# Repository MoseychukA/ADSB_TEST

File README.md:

# ADSB_TEST
ADSB decoder RP2040

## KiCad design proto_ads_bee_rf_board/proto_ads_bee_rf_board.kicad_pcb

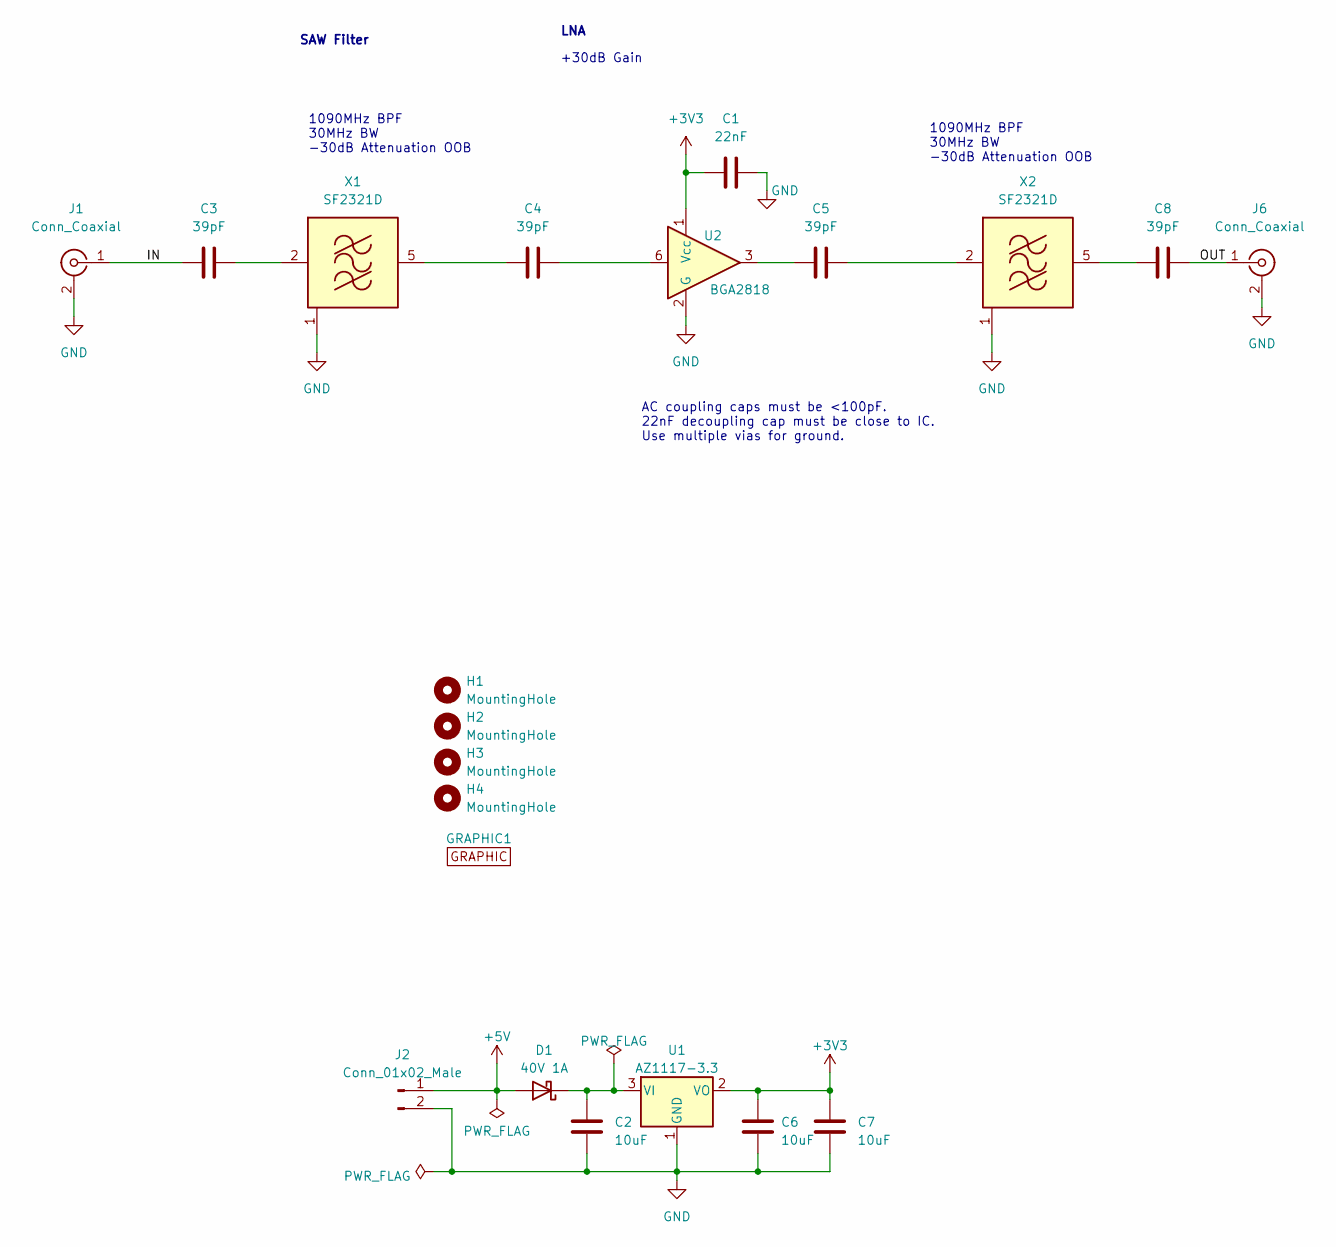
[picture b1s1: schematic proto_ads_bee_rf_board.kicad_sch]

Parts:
C1: 22nF; C_0603_1608Metric
C2, C6, C7: 10uF; C_0805_2012Metric
C3, C4, C5, C8: 39pF; C_0603_1608Metric
D1: 40V 1A; D_DO-41_SOD81_P7.62mm_Horizontal; MPN 1N5819
GRAPHIC1: Graphic; bird_with_pants_small_flipped
H1, H2, H3, H4: MountingHole; MountingHole_3.2mm_M3
J1, J6: Conn_Coaxial; SMA_Amphenol_132289_EdgeMount; MPN 132289
J2: Conn_01x02_Male; PinHeader_1x02_P2.54mm_Horizontal
U1: AZ1117-3.3; SOT-223-3_TabPin2
U2: BGA2818; SOT-363_SC-70-6
X1, X2: SF2321D; Filter_SAW-6_3.8x3.8mm; MPN SF2321D

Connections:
+3V3: C1.1, C6.1, C7.1, U1.2 (VO), U2.1 (Vcc)
+5V: D1.2 (A), J2.1
/IN: C3.1, J1.1 (In)
/OUT: C8.2, J6.1 (In)
GND: C1.2, C2.2, C6.2, C7.2, J1.2 (Ext), J2.2, J6.2 (Ext), U1.1 (GND), U2.2 (G), U2.4 (G), U2.5 (G), X1.1 (GND), X1.3 (GND), X1.4 (GND), X1.6 (GND), X2.1 (GND), X2.3 (GND), X2.4 (GND), X2.6 (GND)
unnamed: C4.2, U2.6
unnamed: C5.1, U2.3
unnamed: C2.1, D1.1 (K), U1.3 (VI)
unnamed: C3.2, X1.2 (IN)
unnamed: C4.1, X1.5 (OUT)
unnamed: C5.2, X2.2 (IN)
unnamed: C8.1, X2.5 (OUT)

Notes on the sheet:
LNA
+30dB Gain
1090MHz BPF 30MHz BW -30dB Attenuation OOB
SAW Filter
AC coupling caps must be <100pF. 22nF decoupling cap must be close to IC. Use multiple vias for ground.

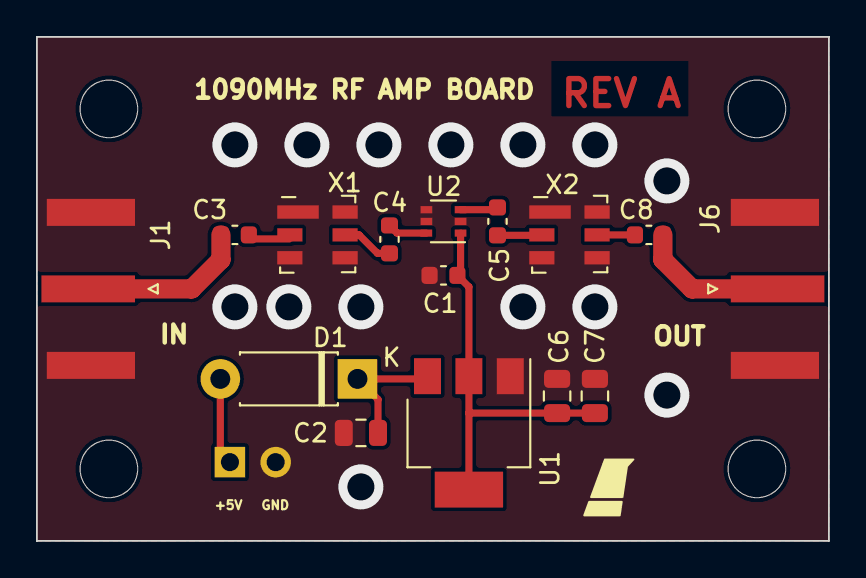
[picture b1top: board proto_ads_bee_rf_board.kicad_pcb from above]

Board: 2 copper layers, 44.0 x 28.0 mm, 21 parts (1 on the bottom side), 12 nets.

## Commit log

2025-06-20 ADSB decoder RP2040
2025-07-09 Receiver 1090
